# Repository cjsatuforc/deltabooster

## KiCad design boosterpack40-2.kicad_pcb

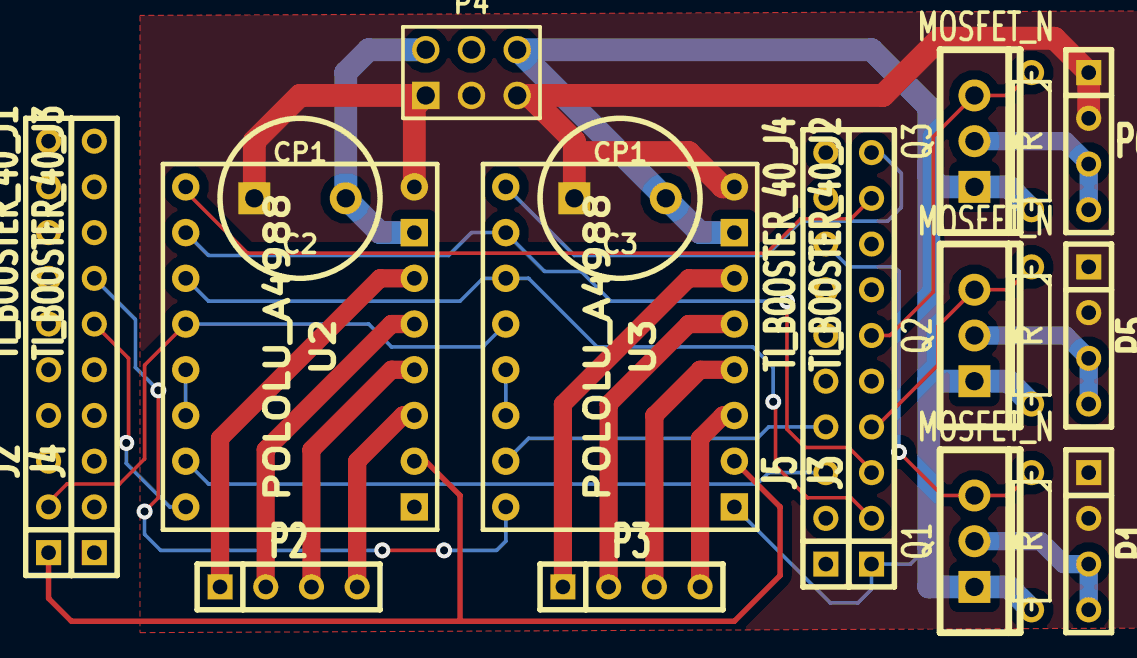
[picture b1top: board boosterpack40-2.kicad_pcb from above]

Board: 2 copper layers, 20 parts (0 on the bottom side), 28 nets.

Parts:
C2, C3: CP1; C2V8
J2: TI_BOOSTER_40_J1; SIL-10
J3: TI_BOOSTER_40_J2; SIL-10
J4: TI_BOOSTER_40_J3; SIL-10
J5: TI_BOOSTER_40_J4; SIL-10
P1, P2, P3, P5, P6: CONN_4; SIL-4
P4: CONN_3X2; pin_array_3x2
Q1, Q2, Q3: MOSFET_N; TO220_VERT
R1, R2, R3: R; R3
U2, U3: POLOLU_A4988; SWDIP8_.6W

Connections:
+24V: C2.1, C3.1, P1.1, P1.2, P4.1, P4.3, P4.5, P5.1, P5.2, P6.1, P6.2, U2.8, U3.8
/BHEAT: J5.8, R1.1
/E1DIR: J4.6, U2.16
/E1EN: J3.9, U2.9
/E1HEAT: J3.4, R2.1
/E1STEP: J5.3, U2.15
/E2DIR: J4.7, U3.16
/E2EN: J3.10, U3.9
/E2HEAT: J3.6, R3.1
/E2STEP: J5.4, U3.15
/EMS1: J2.2, U2.12, U3.12
/EMS2: J3.2, U2.11, U3.11
/EMS3: J3.3, U2.10, U3.10
GND: C2.2, C3.2, J3.1, J4.2, P4.2, P4.4, P4.6, R1.2, R2.2, R3.2, U2.1, U2.7, U3.1, U3.7
unnamed: U2.13, U2.14
unnamed: P3.1, U3.6
unnamed: P2.1, U2.6
unnamed: P2.2, U2.5
unnamed: P2.3, U2.4
unnamed: P2.4, U2.3
unnamed: P5.3, P5.4
unnamed: P6.3, P6.4
unnamed: P3.2, U3.5
unnamed: P1.3, P1.4
unnamed: U3.13, U3.14
unnamed: P3.4, U3.3
unnamed: P3.3, U3.4
VCC: J2.1, U2.2, U3.2

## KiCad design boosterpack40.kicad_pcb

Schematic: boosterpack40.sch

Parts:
C1, C2, C3, C4, C5, C6: CP1; C2V8
J1: CONN_3; SIL-3
J2: TI_BOOSTER_40_J1; SIL-10
J3: TI_BOOSTER_40_J2; SIL-10
J4: TI_BOOSTER_40_J3; SIL-10
J5: TI_BOOSTER_40_J4; SIL-10
K1, K2, K3: CONN_3; SIL-3
P1, P2, P3, P8: CONN_4; SIL-4
P4: CONN_3X2; pin_array_3x2
P5, P6, P7: CONN_2; SIL-2
R1, R2, R3: R; R3
U1, U2, U3: POLOLU_A4988; SWDIP8_.6W

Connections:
+24V: C1.1, C2.1, C3.1, P4.1, P4.3, P4.5, P8.1, P8.2, U1.8 (VMOT), U2.8 (VMOT), U3.8 (VMOT)
/DIR1: J4.8, U3.16 (DIR)
/DIR2: J4.9, U2.16 (DIR)
/DIR3: J4.10, U1.16 (DIR)
/E1TEMP: C4.1, J4.3, P5.1, R1.2
/E2TEMP: C5.1, J4.4, P6.1, R2.2
/ENDSTOP1: J2.8, K1.2
/ENDSTOP2: J2.9, K2.2
/ENDSTOP3: J2.10, K3.2
/MS1: J2.7, U1.12 (MS3), U2.12 (MS3), U3.12 (MS3)
/MS2: J2.6, U1.11 (MS2), U2.11 (MS2), U3.11 (MS2)
/MS3: J2.5, U1.10 (MS1), U2.10 (MS1), U3.10 (MS1)
/STEP1: J5.5, U3.15 (STEP)
/STEP2: J5.6, U2.15 (STEP)
/STEP3: J5.7, U1.15 (STEP)
/XYZEN: U1.9 (EN), U2.9 (EN), U3.9 (EN)
GND: C1.2, C2.2, C3.2, C4.2, C5.2, C6.2, J1.2, J1.3, J3.1, J4.2, K1.3, K2.3, K3.3, P4.2, P4.4, P4.6, P5.2, P6.2, P7.2, P8.3, P8.4, U1.1 (GND), U1.7 (GND), U2.1 (GND), U2.7 (GND), U3.1 (GND), U3.7 (GND)
unnamed: P3.4, U3.3 (IB)
unnamed: U2.13 (RST), U2.14 (SLP)
unnamed: P3.1, U3.6 (2B)
unnamed: P3.2, U3.5 (2A)
unnamed: P3.3, U3.4 (1A)
unnamed: U3.13 (RST), U3.14 (SLP)
unnamed: P2.3, U2.4 (1A)
unnamed: U1.13 (RST), U1.14 (SLP)
unnamed: P2.1, U2.6 (2B)
unnamed: P2.2, U2.5 (2A)
unnamed: P2.4, U2.3 (IB)
unnamed: C6.1, P7.1, R3.2
unnamed: P1.2, U1.5 (2A)
unnamed: P1.1, U1.6 (2B)
unnamed: P1.3, U1.4 (1A)
unnamed: P1.4, U1.3 (IB)
VCC: J1.1, J2.1, K1.1, K2.1, K3.1, R1.1, R2.1, R3.1, U1.2 (VDD), U2.2 (VDD), U3.2 (VDD)

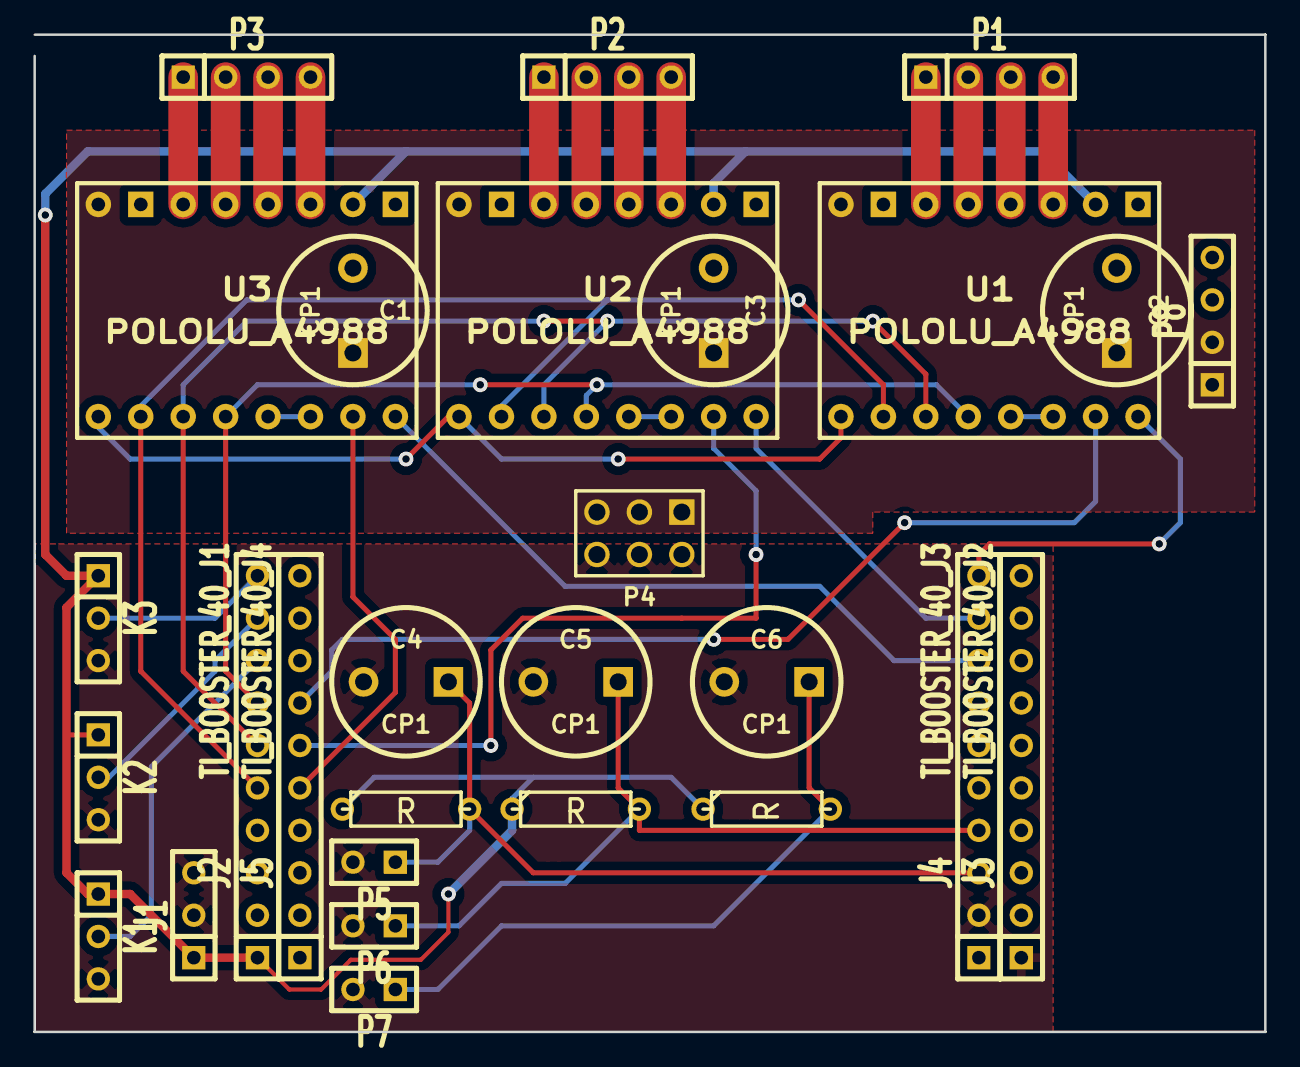
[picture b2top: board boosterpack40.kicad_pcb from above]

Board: 2 copper layers, 73.7 x 59.7 mm, 28 parts (0 on the bottom side), 34 nets.

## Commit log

2013-01-02 Initial Commit. Probably some files in here that we don't want.
